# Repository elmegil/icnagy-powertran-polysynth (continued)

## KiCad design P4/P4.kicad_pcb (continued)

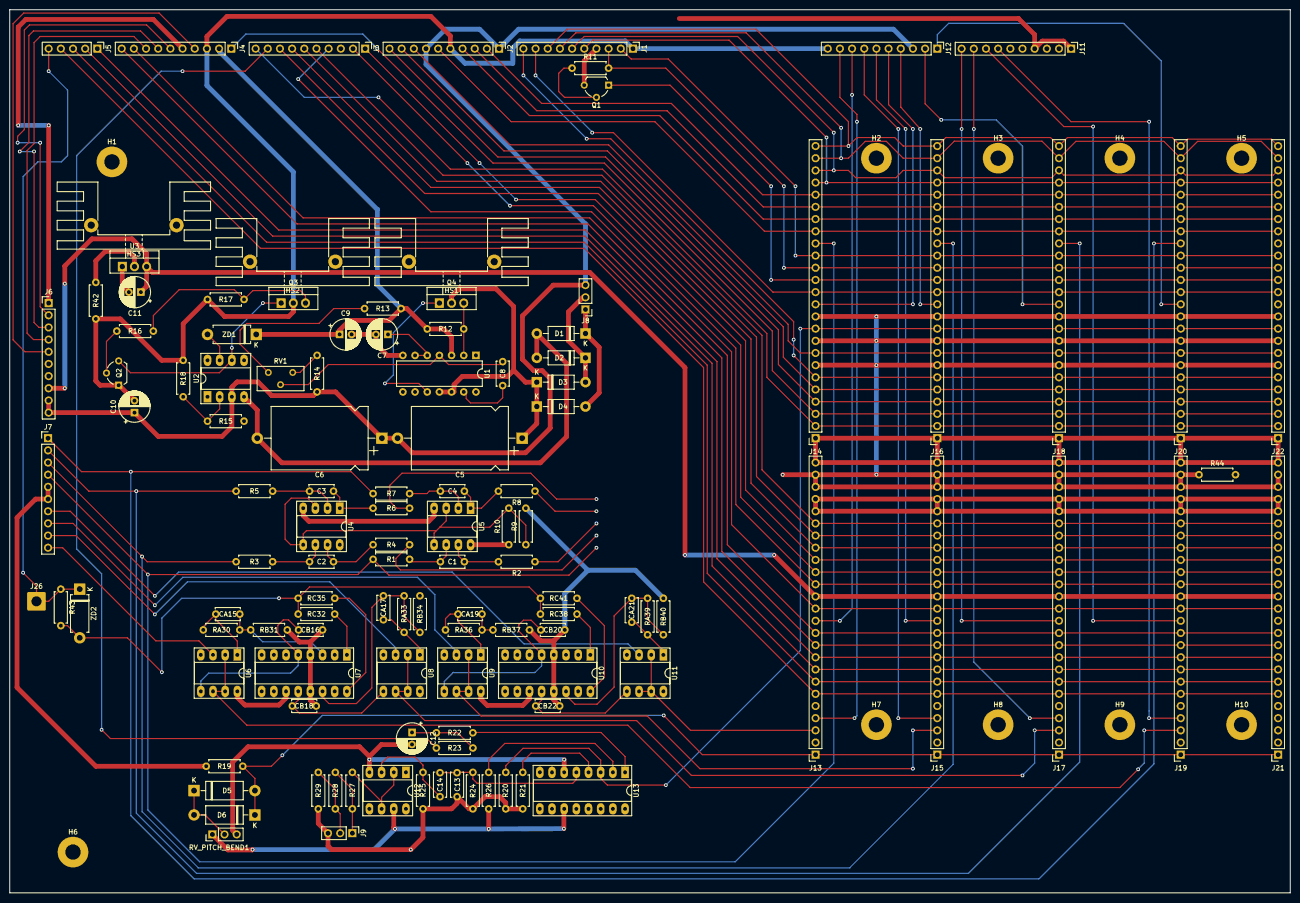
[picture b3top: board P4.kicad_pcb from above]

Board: 2 copper layers, 267.2 x 184.3 mm, 128 parts (0 on the bottom side), 126 nets.

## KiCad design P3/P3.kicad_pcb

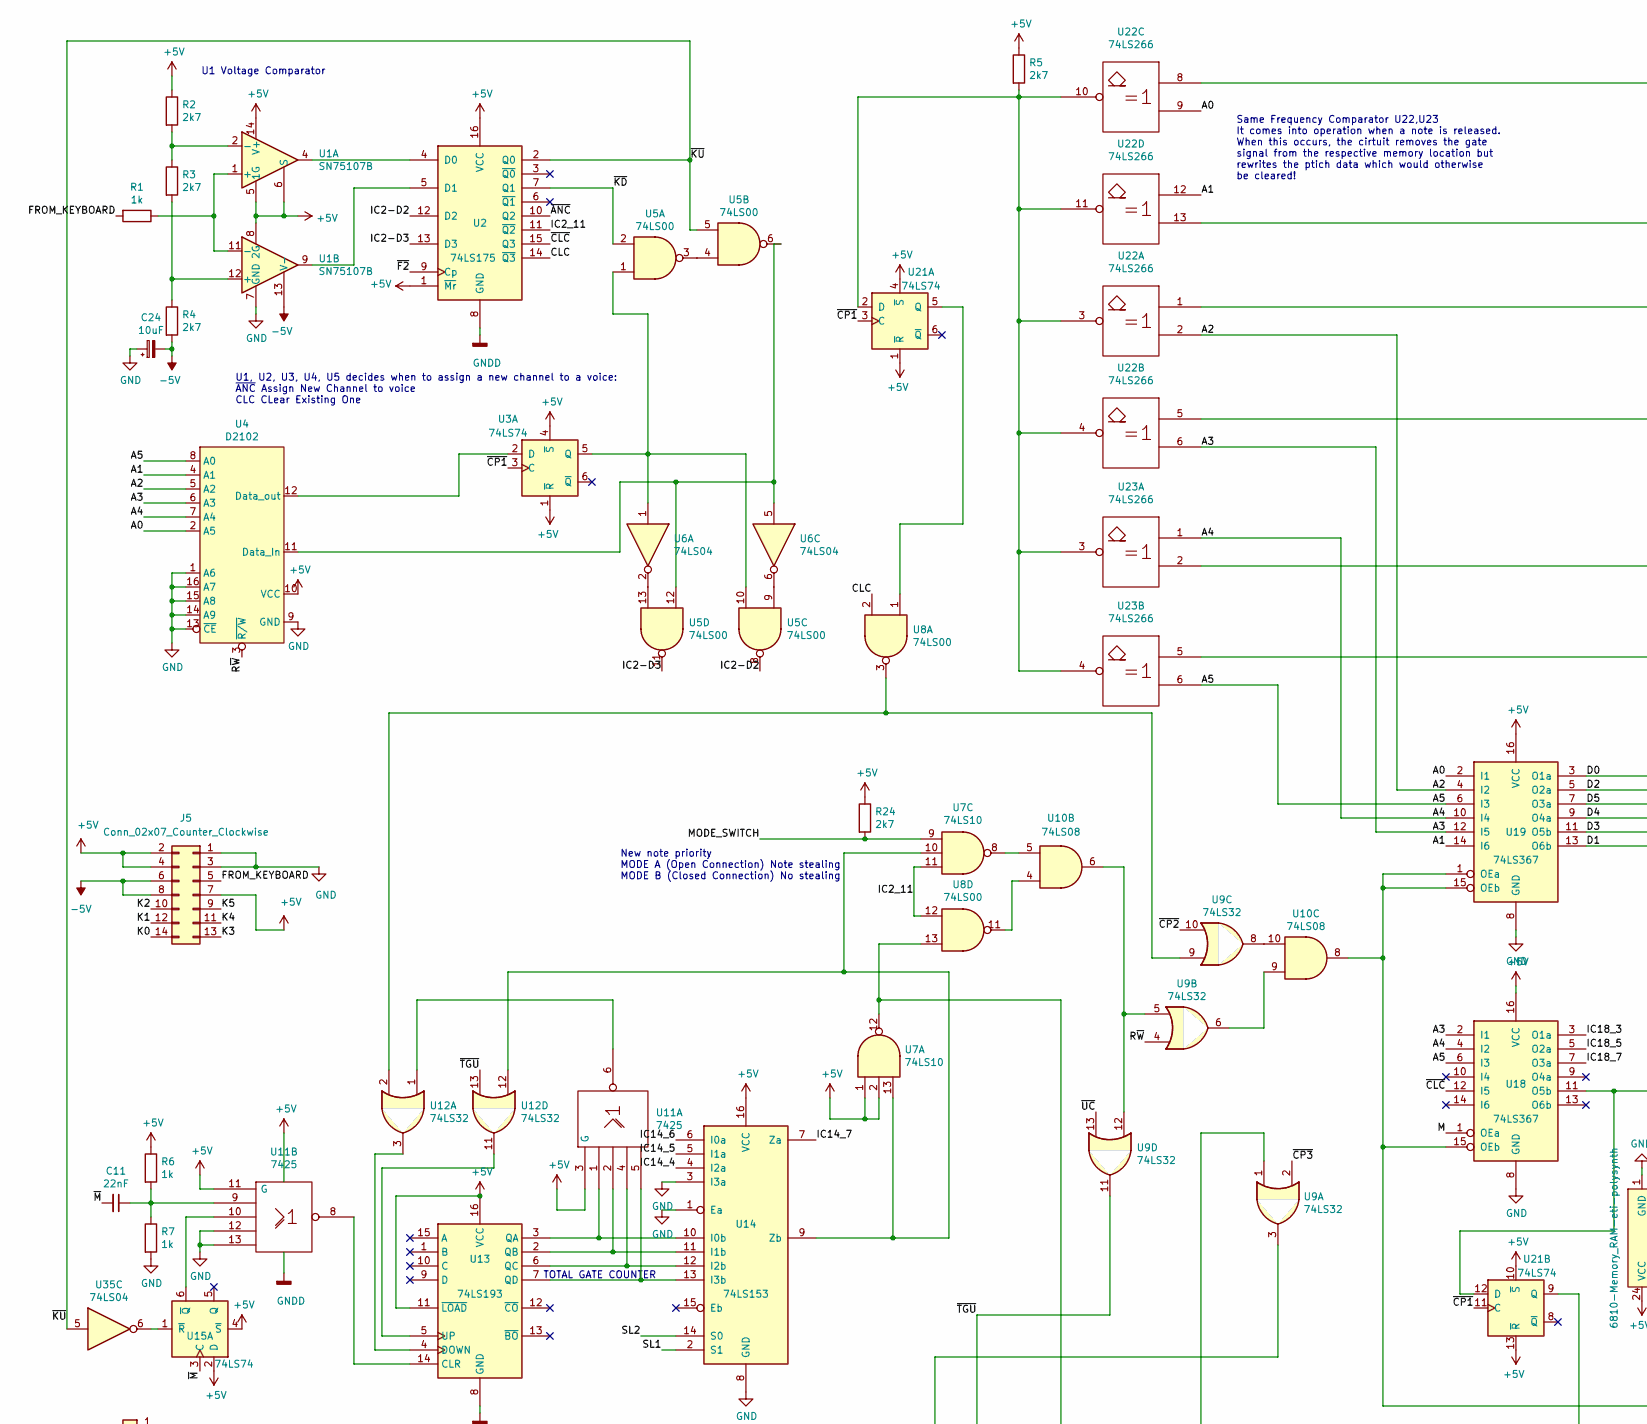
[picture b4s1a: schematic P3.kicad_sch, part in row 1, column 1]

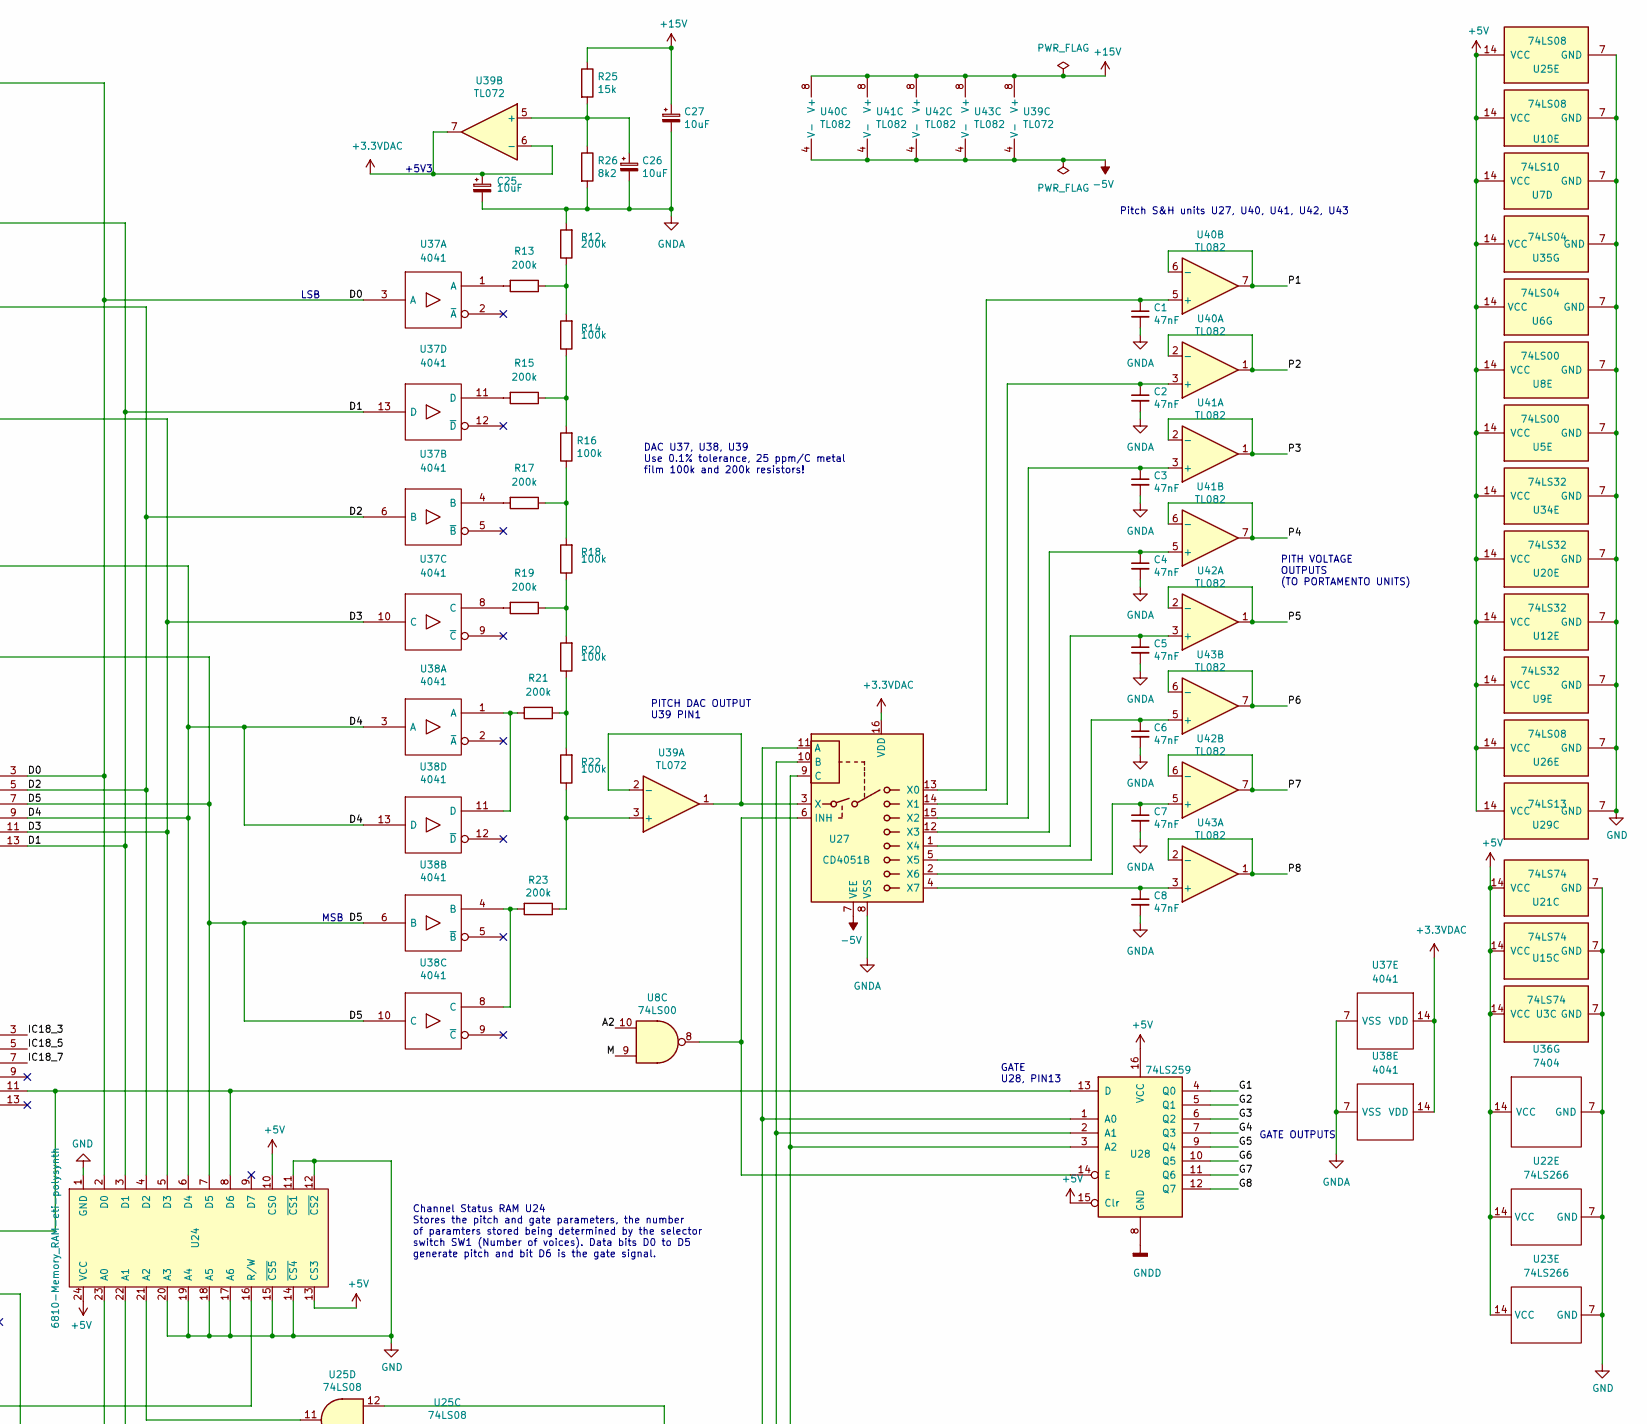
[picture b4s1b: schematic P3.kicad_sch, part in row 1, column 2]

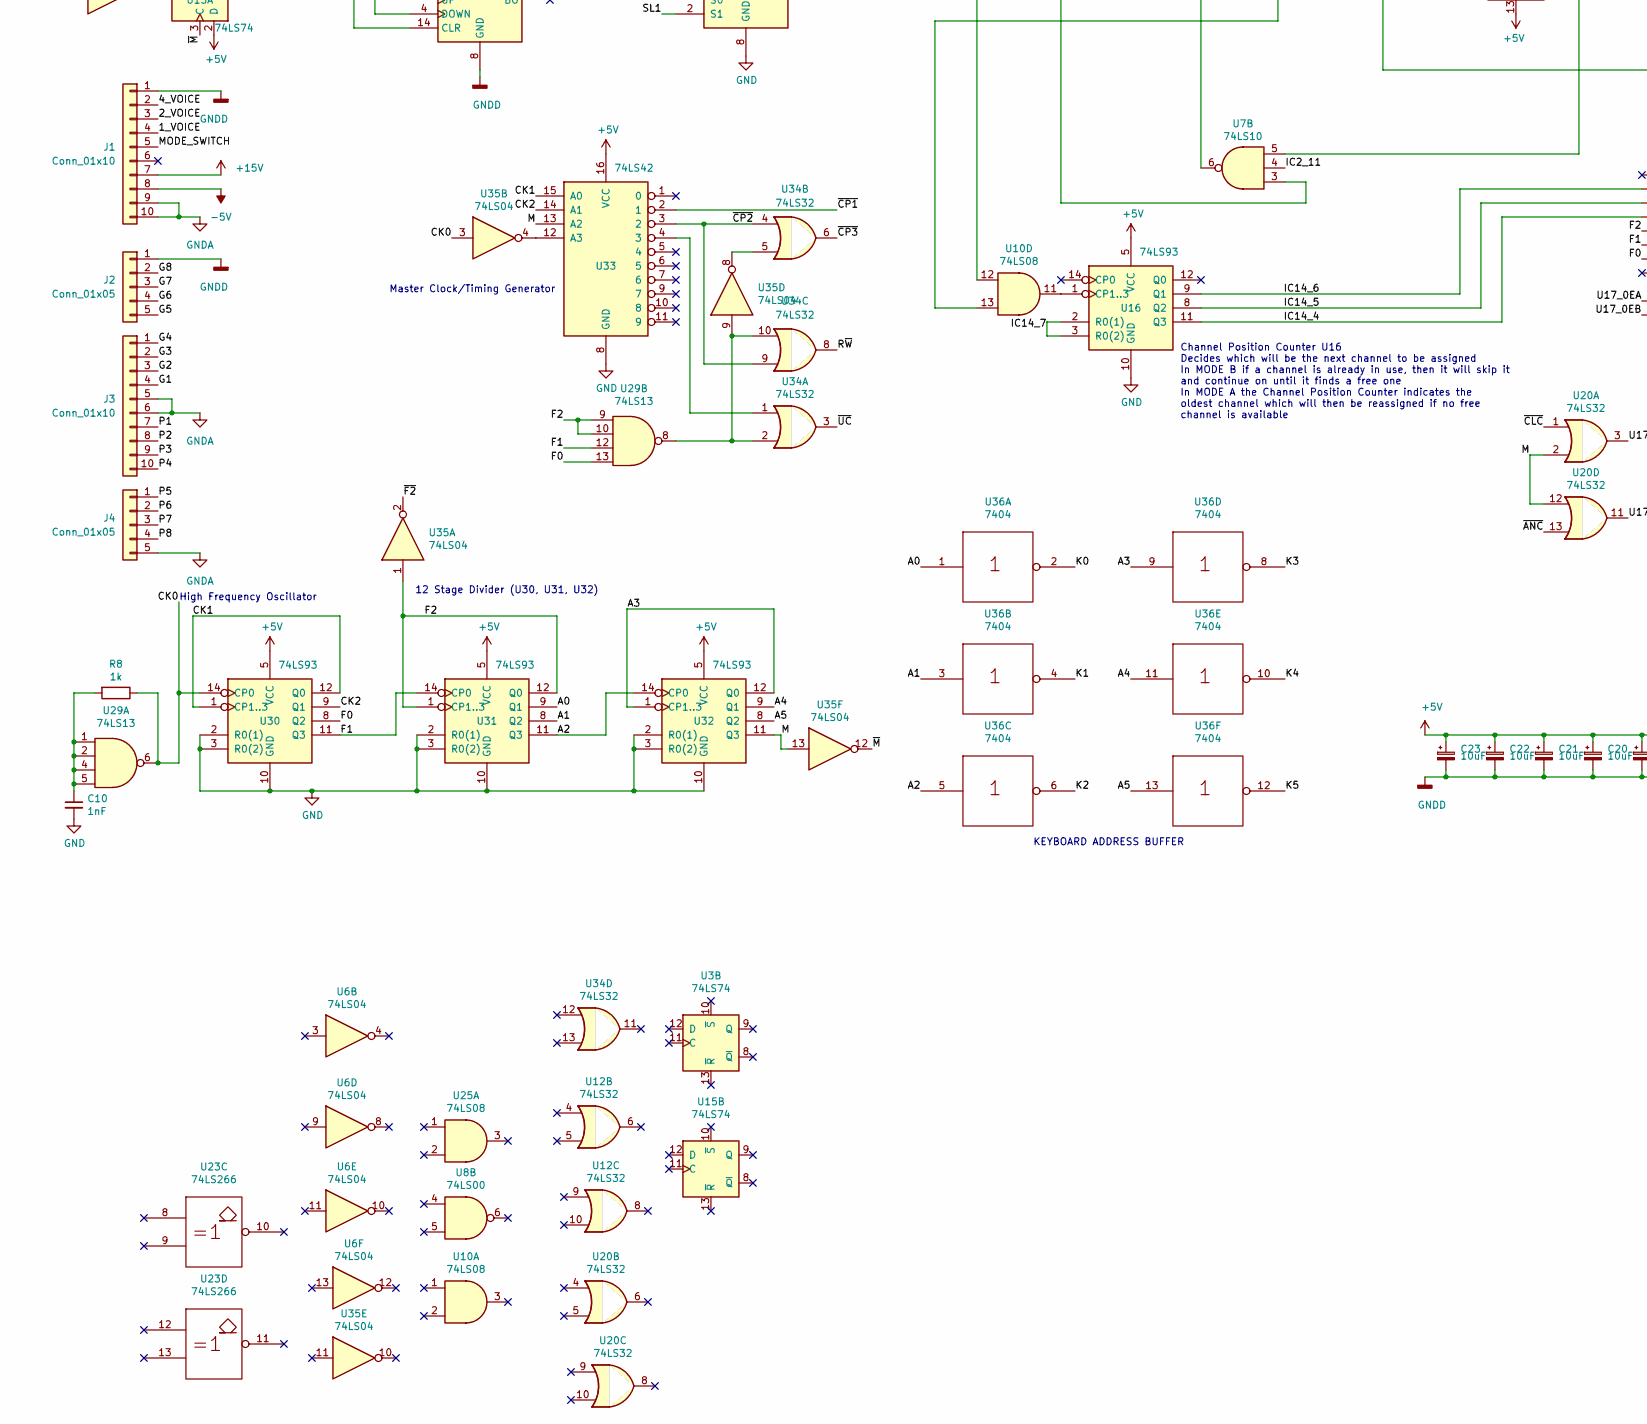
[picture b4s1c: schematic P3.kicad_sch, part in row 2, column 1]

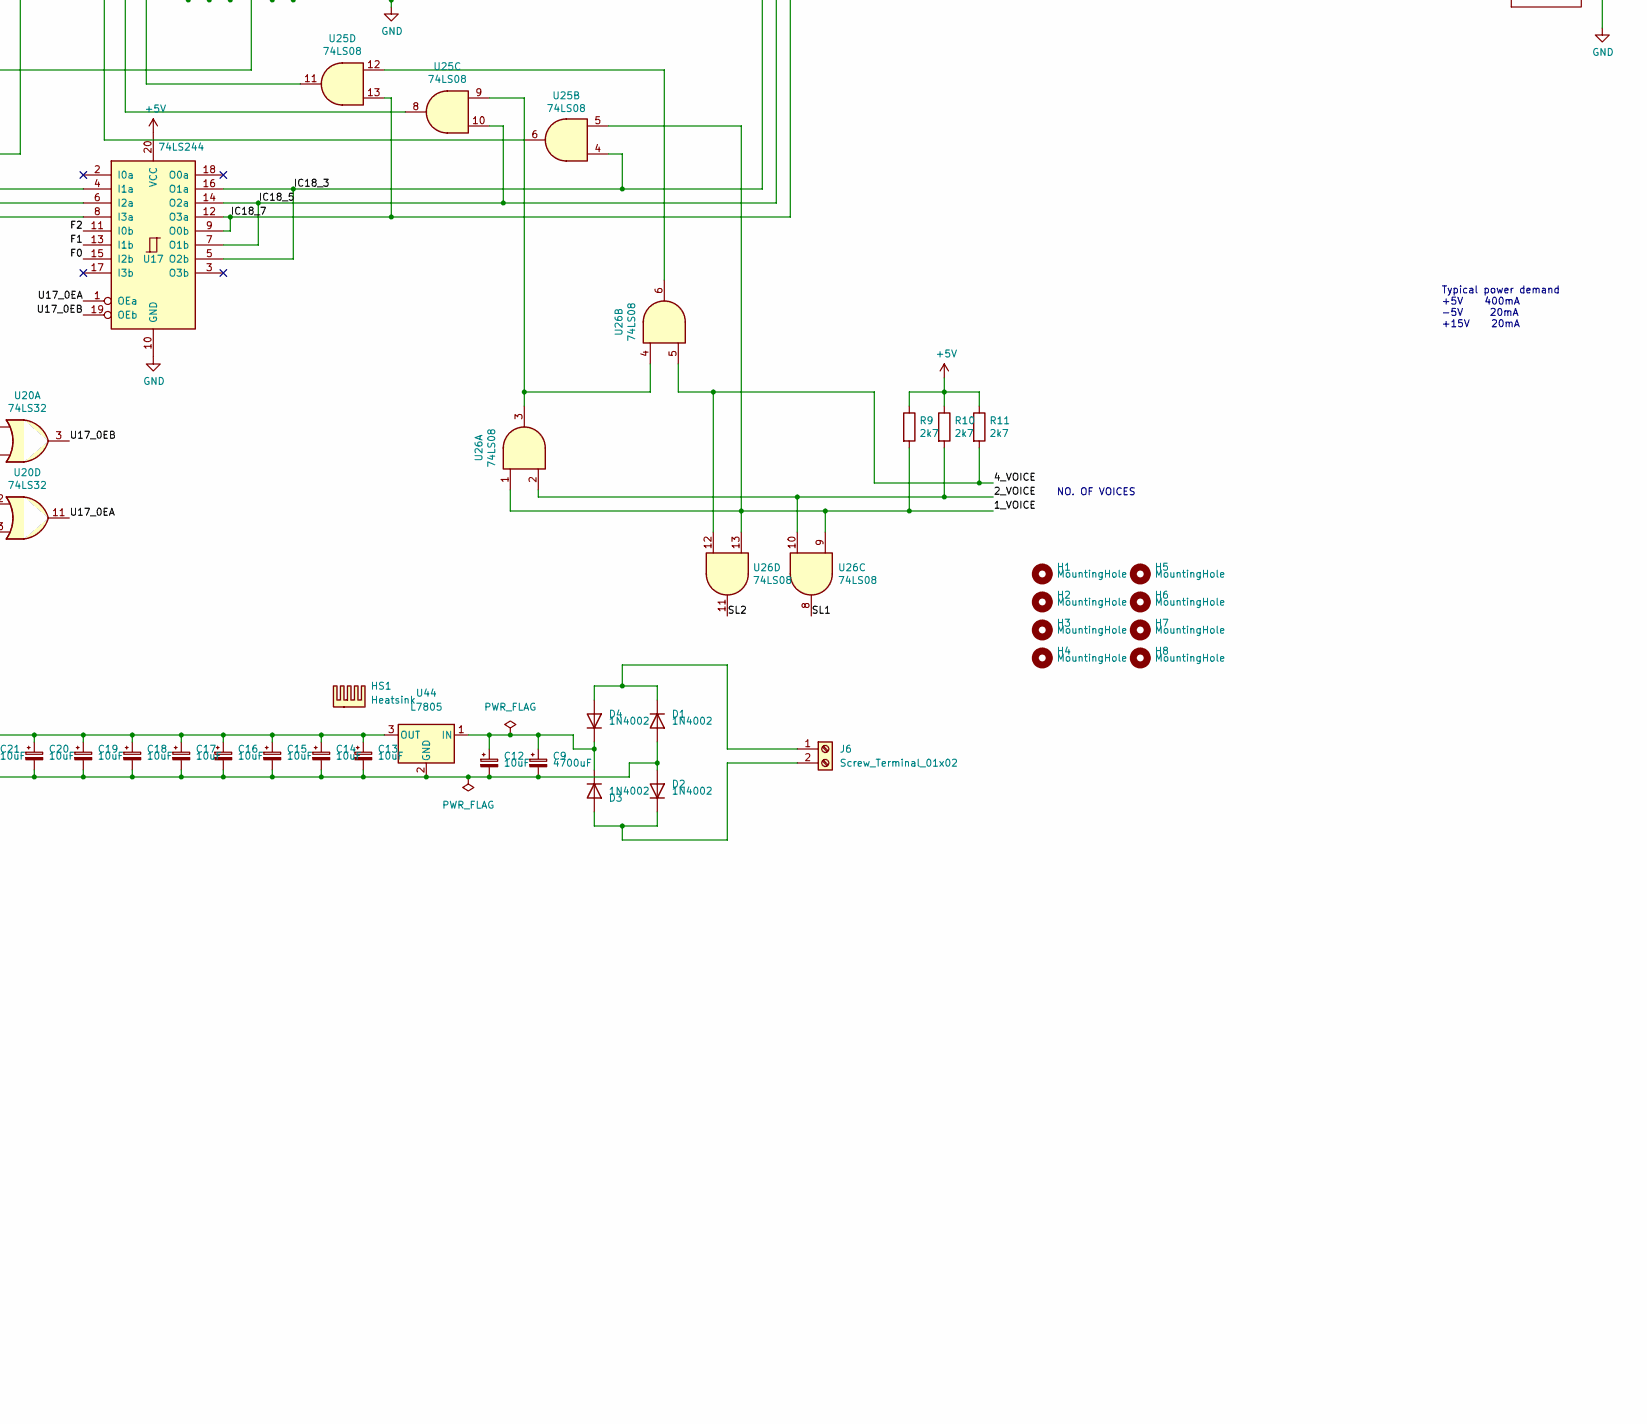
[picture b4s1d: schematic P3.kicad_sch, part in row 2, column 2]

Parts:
C1, C2, C3, C4, C5, C6, C7, C8: 47nF; C_Disc_D7.0mm_W2.5mm_P5.00mm
C9: 4700uF; CP_Axial_L55.0mm_D23.0mm_P60.00mm_Horizontal
C10: 1nF; C_Disc_D7.0mm_W2.5mm_P5.00mm
C11: 22nF; C_Disc_D7.0mm_W2.5mm_P5.00mm
C12, C13, C14, C15, C16, C17, C18, C19, C20, C21, C22, C23, C24, C25, C26, C27: 10uF; CP_Radial_D4.0mm_P2.00mm
D1, D2, D3, D4: 1N4002; D_DO-41_SOD81_P10.16mm_Horizontal
H1, H2, H3, H4, H5, H6, H7, H8: MountingHole; MountingHole_3.2mm_M3_DIN965_Pad
HS1: Heatsink; Heatsink_Fischer_SK129-STS_42x25mm_2xDrill2.5mm
J1, J3: Conn_01x10; PinSocket_1x10_P2.54mm_Vertical
J2, J4: Conn_01x05; PinSocket_1x05_P2.54mm_Vertical
J5: Conn_02x07_Counter_Clockwise; PinSocket_2x07_P2.54mm_Vertical
J6: Screw_Terminal_01x02; TerminalBlock_Altech_AK300-2_P5.00mm
R1, R6, R7, R8: 1k; R_Axial_DIN0207_L6.3mm_D2.5mm_P10.16mm_Horizontal
R2, R3, R4, R5, R9, R10, R11, R24: 2k7; R_Axial_DIN0207_L6.3mm_D2.5mm_P10.16mm_Horizontal
R12, R13, R15, R17, R19, R21, R23: 200k; R_Axial_DIN0207_L6.3mm_D2.5mm_P10.16mm_Horizontal
R14, R16, R18, R20, R22: 100k; R_Axial_DIN0207_L6.3mm_D2.5mm_P10.16mm_Horizontal
R25: 15k; R_Axial_DIN0207_L6.3mm_D2.5mm_P10.16mm_Horizontal
R26: 8k2; R_Axial_DIN0207_L6.3mm_D2.5mm_P10.16mm_Horizontal
U1: SN75107B; DIP-14_W7.62mm_LongPads
U2: 74LS175; DIP-16_W7.62mm_LongPads
U3, U15, U21: 74LS74; DIP-14_W7.62mm_LongPads
U4: D2102; DIP-16_W7.62mm_LongPads
U5, U8: 74LS00; DIP-14_W7.62mm_LongPads
U6, U35: 74LS04; DIP-14_W7.62mm_LongPads
U7: 74LS10; DIP-14_W7.62mm_LongPads
U9, U12, U20, U34: 74LS32; DIP-14_W7.62mm_LongPads
U10, U25, U26: 74LS08; DIP-14_W7.62mm_LongPads
U11: 7425; DIP-14_W7.62mm_LongPads
U13: 74LS193; DIP-16_W7.62mm_LongPads
U14: 74LS153; DIP-16_W7.62mm_LongPads
U16, U30, U31, U32: 74LS93; DIP-14_W7.62mm_LongPads
U17: 74LS244; DIP-20_W7.62mm_LongPads
U18, U19: 74LS367; DIP-16_W7.62mm_LongPads
U22, U23: 74LS266; DIP-14_W7.62mm_LongPads
U24: 6810-Memory_RAM-eti-polysynth; DIP-24_W15.24mm_LongPads
U27: CD4051B; DIP-16_W7.62mm_LongPads
U28: 74LS259; DIP-16_W7.62mm_LongPads
U29: 74LS13; DIP-14_W7.62mm_LongPads
U33: 74LS42; DIP-16_W7.62mm_LongPads
U36: 7404; DIP-14_W7.62mm_LongPads
U37, U38: 4041; DIP-14_W7.62mm_LongPads
U39: TL072; DIP-8_W7.62mm_LongPads
U40, U41, U42, U43: TL082; DIP-8_W7.62mm_LongPads
U44: L7805; TO-220-3_Vertical

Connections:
+15V: C27.1, J1.7, R25.1, U39.8 (V+), U40.8 (V+), U41.8 (V+), U42.8 (V+), U43.8 (V+)
-5V: C24.2, J1.8, J5.6, J5.8, R4.2, U1.13 (V-), U27.7 (VEE), U39.4 (V-), U40.4 (V-), U41.4 (V-), U42.4 (V-), U43.4 (V-)
/1_VOICE: J1.4, R9.2, U25.5, U26.1, U26.9, U26.13
/2_VOICE: J1.3, R10.2, U26.2, U26.10
/4_VOICE: J1.2, R11.2, U26.5, U26.12
/A0: U4.2 (A5), U19.2 (I1), U22.9, U31.9 (Q1), U36.1
/A1: U4.4 (A1), U19.14 (I6), U22.12, U31.8 (Q2), U36.3
/A2: U4.5 (A2), U8.10, U19.4 (I2), U22.2, U31.11 (Q3), U32.14 (CP0), U36.5
/A3: U4.6 (A3), U18.2 (I1), U19.12 (I5), U22.6, U32.1 (CP1..3), U32.12 (Q0), U36.9
/A4: U4.7 (A4), U18.4 (I2), U19.10 (I4), U23.1, U32.9 (Q1), U36.11
/A5: U4.8 (A0), U18.6 (I3), U19.6 (I3), U23.6, U32.8 (Q2), U36.13
/CK0: R8.1, U29.6, U30.14 (CP0), U35.3
/CK1: U30.1 (CP1..3), U30.12 (Q0), U33.15 (A0)
/CK2: U30.9 (Q1), U33.14 (A1)
/CLC: U2.14 (~Q3), U8.2
/D0: U19.3 (O1a), U22.8, U24.2 (D0), U37.3 (A)
/D1: U19.13 (O6b), U22.13, U24.3 (D1), U37.13 (D)
/D2: U19.5 (O2a), U22.1, U24.4 (D2), U37.6 (B)
/D3: U19.11 (O5b), U22.5, U24.5 (D3), U37.10 (C)
/D4: U19.9 (O4a), U23.2, U24.6 (D4), U38.3 (A), U38.13 (D)
/D5: U19.7 (O3a), U23.5, U24.7 (D5), U38.6 (B), U38.10 (C)
/F0: U17.15 (I2b), U29.13, U30.8 (Q2)
/F1: U17.13 (I1b), U29.12, U30.11 (Q3), U31.14 (CP0)
/F2: U17.11 (I0b), U29.9, U29.10, U31.1 (CP1..3), U31.12 (Q0), U35.1
/FROM_KEYBOARD: J5.5, R1.2
/G1: J3.4, U28.4 (Q0)
/G2: J3.3, U28.5 (Q1)
/G3: J3.2, U28.6 (Q2)
/G4: J3.1, U28.7 (Q3)
/G5: J2.5, U28.9 (Q4)
/G6: J2.4, U28.10 (Q5)
/G7: J2.3, U28.11 (Q6)
/G8: J2.2, U28.12 (Q7)
/IC2-D2: U2.12 (D2), U5.8
/IC2-D3: U2.13 (D3), U5.11
/IC2_11: U2.11 (~Q2), U7.4, U7.11, U8.12
/IC14_4: U14.4 (I2a), U16.11 (Q3), U17.8 (I3a)
/IC14_5: U14.5 (I1a), U16.8 (Q2), U17.6 (I2a)
/IC14_6: U14.6 (I0a), U16.9 (Q1), U17.4 (I1a)
/IC14_7: U14.7 (Za), U16.2 (R0(1)), U16.3 (R0(2))
/IC18_3: U17.5 (O2b), U17.16 (O1a), U18.3 (O1a), U25.4, U27.11 (A), U28.1 (A0)
/IC18_5: U17.7 (O1b), U17.14 (O2a), U18.5 (O2a), U25.10, U27.10 (B), U28.2 (A1)
/IC18_7: U17.9 (O0b), U17.12 (O3a), U18.7 (O3a), U25.13, U27.9 (C), U28.3 (A2)
/K0: J5.14, U36.2
/K1: J5.12, U36.4
/K2: J5.10, U36.6
/K3: J5.13, U36.8
/K4: J5.11, U36.10
/K5: J5.9, U36.12
/M: U8.9, U18.1 (OEa), U20.2, U20.12, U32.11 (Q3), U33.13 (A2), U35.13
/MODE_SWITCH: J1.5, R24.2, U7.9
/P1: J3.7, U40.6 (-), U40.7
/P2: J3.8, U40.1, U40.2 (-)
/P3: J3.9, U41.1, U41.2 (-)
/P4: J3.10, U41.6 (-), U41.7
/P5: J4.1, U42.1, U42.2 (-)
/P6: J4.2, U43.6 (-), U43.7
/P7: J4.3, U42.6 (-), U42.7
/P8: J4.4, U43.1, U43.2 (-)
/R~W: U4.3 (~R/W), U9.4, U34.8
/SL1: U14.2 (S1), U26.8
/SL2: U14.14 (S0), U26.11
/U17_0EA: U17.1 (OEa), U20.11
/U17_0EB: U17.19 (OEb), U20.3
/~ANC: U2.10 (Q2), U20.13
/~CLC: U2.15 (Q3), U18.12 (I5), U20.1
/~CP1: U3.3 (C), U21.3 (C), U21.11 (C), U33.2 (1)
/~CP2: U9.10, U33.3 (2), U34.4, U34.9
/~CP3: U9.2, U34.6
/~F2: U2.9 (Cp), U35.2
/~KD: U2.7 (Q1), U5.2
/~KU: U2.2 (Q0), U5.5, U35.5
/~M: C11.2, U15.3 (C), U35.12
/~TGU: U9.11, U10.12, U12.13
/~UC: U9.13, U34.3
unnamed: C1.1, U27.13 (X0), U40.5 (+)
unnamed: C2.1, U27.14 (X1), U40.3 (+)
unnamed: C3.1, U27.15 (X2), U41.3 (+)
unnamed: C4.1, U27.12 (X3), U41.5 (+)
unnamed: C5.1, U27.1 (X4), U42.3 (+)
unnamed: C6.1, U27.5 (X5), U43.5 (+)
unnamed: C7.1, U27.2 (X6), U42.5 (+)
unnamed: C8.1, U27.4 (X7), U43.3 (+)
unnamed: C10.1, R8.2, U29.1, U29.2, U29.4, U29.5
unnamed: C11.1, R6.2, R7.1, U11.9
unnamed: C9.1, C12.1, D3.1 (K), D4.1 (K), U44.1 (IN)
unnamed: C26.1, R25.2, R26.1, U39.5 (+)
unnamed: D1.1 (K), D4.2 (A), J6.1
unnamed: D2.1 (K), D3.2 (A), J6.2
unnamed: R1.1, U1.1 (+), U1.11 (-)
unnamed: R2.2, R3.1, U1.2 (-)
unnamed: R3.2, R4.1, U1.12 (+)
unnamed: R5.2, U21.2 (D), U22.3, U22.4, U22.10, U22.11, U23.3, U23.4
unnamed: R12.1, R13.1, R14.2
unnamed: R13.2, U37.1 (A)
unnamed: R14.1, R15.1, R16.2
unnamed: R15.2, U37.11 (D)
unnamed: R16.1, R17.1, R18.2
unnamed: R17.2, U37.4 (B)
unnamed: R18.1, R19.1, R20.2
unnamed: R19.2, U37.8 (C)
unnamed: R20.1, R21.1, R22.2
unnamed: R21.2, U38.1 (A), U38.11 (D)
unnamed: R22.1, R23.1, U39.3 (+)
unnamed: R23.2, U38.4 (B), U38.8 (C)
unnamed: U1.4, U2.4 (D0)
unnamed: U1.9, U2.5 (D1)
unnamed: U3.2 (D), U4.12 (Data_out)
unnamed: U3.5 (Q), U5.1, U5.10, U6.1
unnamed: U4.11 (Data_In), U5.6, U5.12, U6.5
unnamed: U5.3, U5.4
unnamed: U5.9, U6.6
unnamed: U5.13, U6.2
unnamed: U7.6, U9.1
unnamed: U7.3, U7.12, U8.13
unnamed: U8.11, U10.4
unnamed: U7.8, U10.5
unnamed: U9.5, U9.12, U10.6
unnamed: U10.8, U18.15 (OEb), U19.1 (OEa), U19.15 (OEb), U24.16 (R/W)
unnamed: U9.6, U10.9
unnamed: U9.8, U10.10
unnamed: U10.11, U16.1 (CP1..3)
unnamed: U9.3, U10.13
unnamed: U11.1, U13.3 (QA), U14.10 (I0b)
unnamed: U11.2, U13.2 (QB), U14.11 (I1b)
unnamed: U11.4, U13.6 (QC), U14.12 (I2b)
unnamed: U11.5, U13.7 (QD), U14.13 (I3b)
unnamed: U11.6, U12.1
unnamed: U11.8, U13.14 (CLR)
unnamed: U11.10, U15.6 (~Q)
unnamed: U8.3, U9.9, U12.2
unnamed: U12.3, U13.4 (DOWN)
unnamed: U12.11, U13.5 (UP)
unnamed: U7.10, U7.13, U12.12, U14.9 (Zb)
unnamed: U15.1 (~R), U35.6
unnamed: U18.11 (O5b), U21.12 (D), U24.8 (D6), U28.13 (D)
unnamed: U8.1, U21.5 (Q)
unnamed: U7.5, U21.9 (Q)
unnamed: U24.21 (A2), U25.11
unnamed: U24.22 (A1), U25.8
unnamed: U24.23 (A0), U25.6
unnamed: U25.9, U26.3, U26.4
unnamed: U25.12, U26.6
unnamed: U27.3 (X), U39.1, U39.2 (-)
unnamed: U8.8, U27.6 (INH), U28.14 (E)
unnamed: U29.8, U34.2, U34.10, U35.9
unnamed: U33.4 (3), U34.1
unnamed: U33.12 (A3), U35.4
unnamed: U34.5, U35.8

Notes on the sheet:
GATE OUTPUTS
GATE U28, PIN13
MSB
Typical power demand +5V 400mA -5V 20mA +15V 20mA
Channel Position Counter U16 Decides which will be the next channel to be assigned In MODE B if a channel is already in use, then it will skip it and continue on until it finds a free one In MODE A the Channel Position Counter indicates the oldest channel which will then be reassigned if no free ch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
KEYBOARD ADDRESS BUFFER
PITH VOLTAGE OUTPUTS (TO PORTAMENTO UNITS)
TOTAL GATE COUNTER
Master Clock/Timing Generator
Channel Status RAM U24 Stores the pitch and gate parameters, the number of paramters stored being determined by the selector switch SW1 (Number of voices). Data bits D0 to D5 generate pitch and bit D6 is the gate signal.
U1, U2, U3, U4, U5 decides when to assign a new channel to a voice: ~{ANC} Assign New Channel to voice CLC CLear Existing One
+5V3
Pitch S&H units U27, U40, U41, U42, U43
U1 Voltage Comparator
DAC U37, U38, U39 Use 0.1% tolerance, 25 ppm/C metal film 100k and 200k resistors!
NO. OF VOICES
LSB
New note priority MODE A (Open Connection) Note stealing MODE B (Closed Connection) No stealing
Same Frequency Comparator U22,U23 It comes into operation when a note is released. When this occurs, the cirtuit removes the gate signal from the respective memory location but rewrites the ptich data which would otherwise be cleared!
12 Stage Divider (U30, U31, U32)
PITCH DAC OUTPUT U39 PIN1
High Frequency Oscillator

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
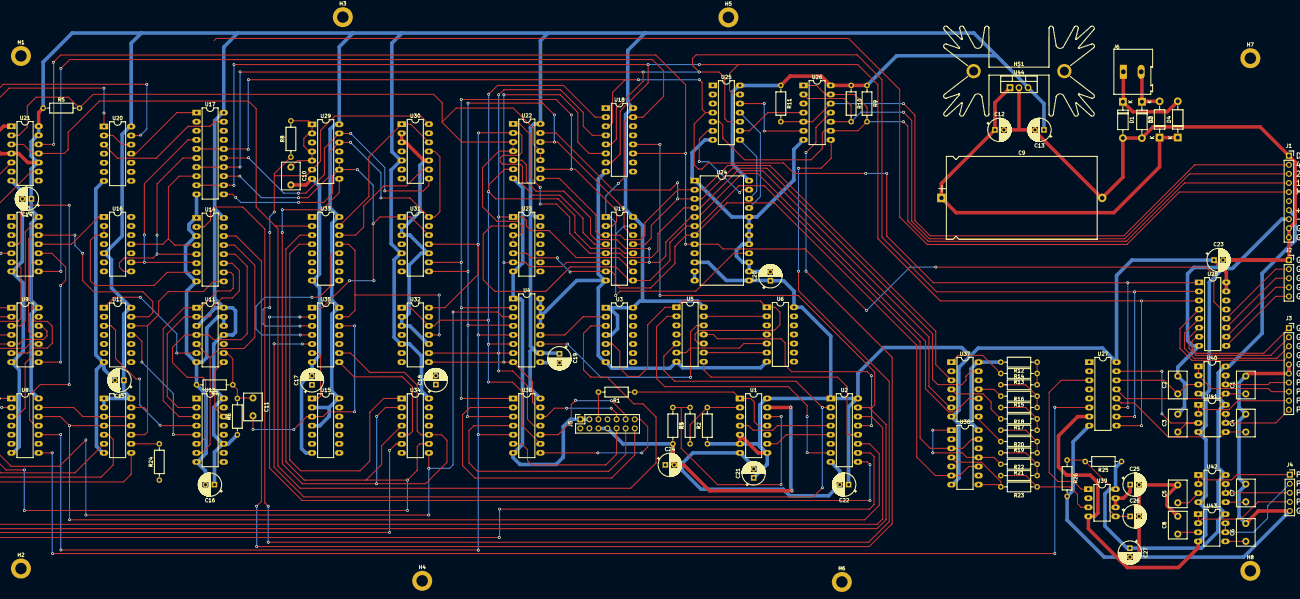
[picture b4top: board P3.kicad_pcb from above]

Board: 2 copper layers, 116 parts (0 on the bottom side), 152 nets.
